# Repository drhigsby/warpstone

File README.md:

# warpstone

KLE: http://www.keyboard-layout-editor.com/#/gists/da9202c4c069f9cc00b6be29940ffcfc

 Warpstone is an 11u traditionally staggered monstrosity of a keyboard with multiple side mod and spacebar options.

* Keyboard Maintainer: [H. Bond](https://github.com/drhigsby)
* Hardware Supported: Warpstone (https://github.com/drhigsby/warpstone)
* Hardware Availability: make your own

Make example for this keyboard (after setting up your build environment):

    make warpstone:default

See the [build environment setup](https://docs.qmk.fm/#/getting_started_build_tools) and the [make instructions](https://docs.qmk.fm/#/getting_started_make_guide) for more information. Brand new to QMK? Start with our [Complete Newbs Guide](https://docs.qmk.fm/#/newbs).

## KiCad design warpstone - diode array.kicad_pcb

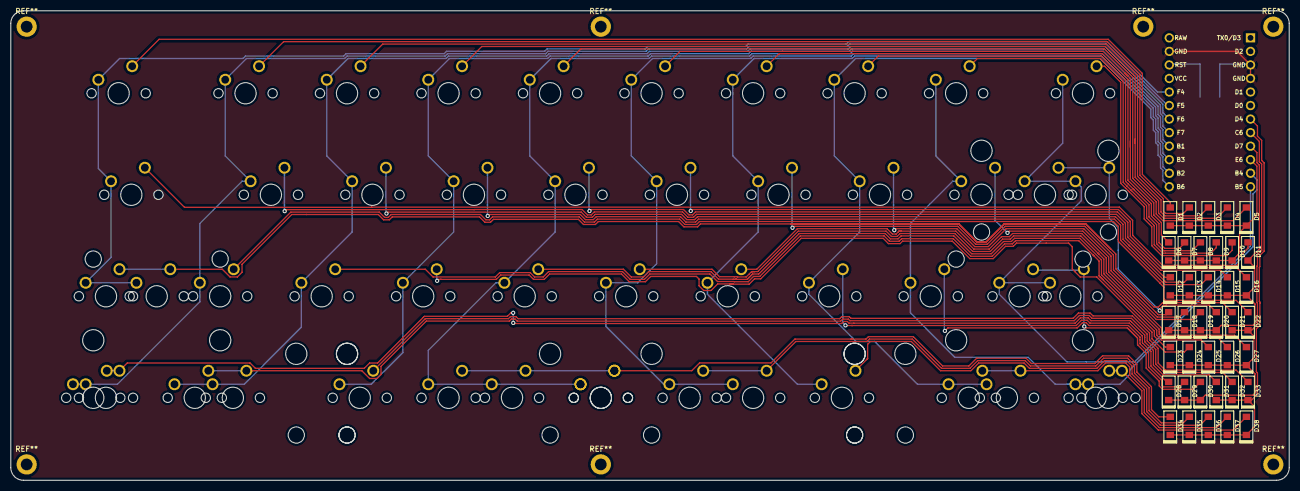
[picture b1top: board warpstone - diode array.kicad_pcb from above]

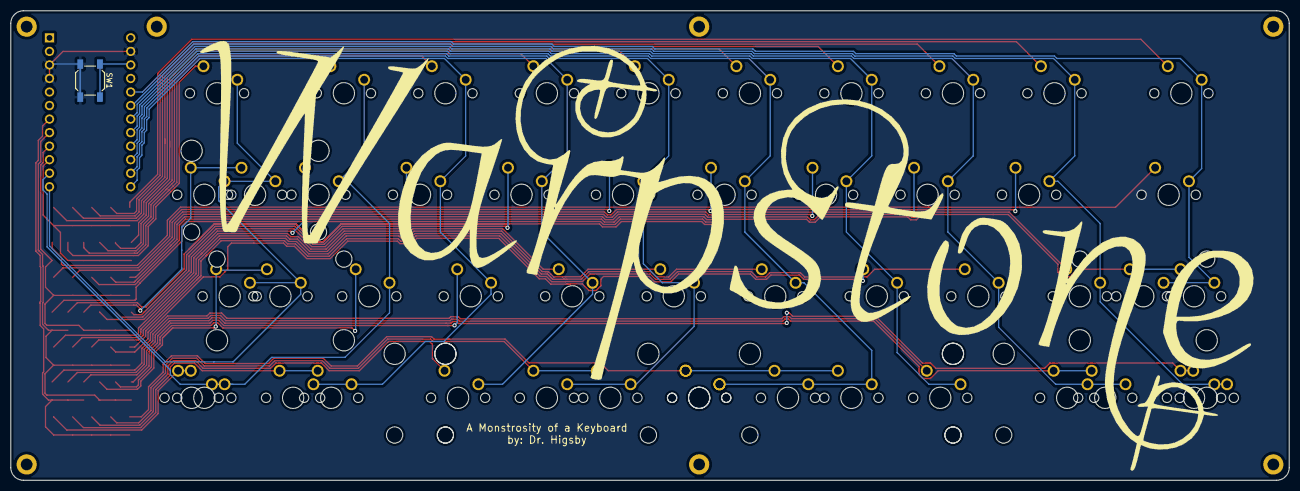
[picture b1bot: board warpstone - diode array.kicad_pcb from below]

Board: 2 copper layers, 239.9 x 88.1 mm, 89 parts (2 on the bottom side), 54 nets.

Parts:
D1, D2, D3, D4, D5, D6, D7, D8, D9, D10, D11, D12, D13, D14, D15, D16, D17, D18, D19, D20, D21, D22, D23, D24, D25, D26, D27, D28, D29, D30, D31, D32, D33, D34, D35, D36, D37, D38: D_Small; D_SOD123
MX1, MX10: MX-NoLED; MXOnly-1.5U-NoLED
MX2, MX3, MX4, MX5, MX6, MX7, MX8, MX9, MX12, MX13, MX14, MX15, MX16, MX17, MX18, MX19, MX22, MX23, MX24, MX25, MX26, MX27, MX28, MX29, MX31-1u1, MX32-1u1, MX37-1u1, MX38-1u1: MX-NoLED; MXOnly-1U-NoLED
MX11, MX30, MX34, MX35: MX-NoLED; MXOnly-1.75U-NoLED
MX20, MX21, MX31, MX32, MX33, MX36, MX37, MX38: MX-NoLED; MXOnly-1.25U-NoLED
MX20-2.25u1: MX-NoLED; MXOnly-2.25U-ReversedStabilizers-NoLED
MX21-2.25u1: MX-NoLED; MXOnly-2.25U-NoLED
MX30-2.75u1: MX-NoLED; MXOnly-2.75U-NoLED
MX34-3u1, MX35-3u1: MX-NoLED; MXOnly-3U-ReversedStabilizers-NoLED
MX34-6u1: MX-NoLED; MXOnly-6U-Centered-ReversedStabilizers-NoLED
MX34-7u1: MX-NoLED; MXOnly-7U-ReversedStabilizers-NoLED
SW1: SW_Push; SW_SPST_SKQG_WithStem
U1: ProMicro; ArduinoProMicro

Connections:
GND: SW1.2, U1.3, U1.4, U1.23
unnamed: D1.2, MX1.2
unnamed: D2.2, MX2.2
unnamed: D3.2, MX3.2
unnamed: D4.2, MX4.2
unnamed: D5.2, MX5.2
unnamed: D6.2, MX6.2
unnamed: D7.2, MX7.2
unnamed: D8.2, MX8.2
unnamed: D9.2, MX9.2
unnamed: D10.2, MX10.2
unnamed: D11.2, MX11.2
unnamed: D12.2, MX12.2
unnamed: D13.2, MX13.2
unnamed: D14.2, MX14.2
unnamed: D15.2, MX15.2
unnamed: D16.2, MX16.2
unnamed: D17.2, MX17.2
unnamed: D18.2, MX18.2
unnamed: D19.2, MX19.2
unnamed: D20.2, MX20.2, MX20-2.25u1.2
unnamed: D21.2, MX21.2, MX21-2.25u1.2
unnamed: D22.2, MX22.2
unnamed: D23.2, MX23.2
unnamed: D24.2, MX24.2
unnamed: D25.2, MX25.2
unnamed: D26.2, MX26.2
unnamed: D27.2, MX27.2
unnamed: D28.2, MX28.2
unnamed: D29.2, MX29.2
unnamed: D30.2, MX30.2, MX30-2.75u1.2
unnamed: D31.2, MX31.2, MX31-1u1.2
unnamed: D32.2, MX32.2, MX32-1u1.2
unnamed: D33.2, MX33.2
unnamed: D34.2, MX34.2, MX34-3u1.2, MX34-6u1.2, MX34-7u1.2
unnamed: D35.2, MX35.2, MX35-3u1.2
unnamed: D36.2, MX36.2
unnamed: D37.2, MX37.2, MX37-1u1.2
unnamed: D38.2, MX38.2, MX38-1u1.2
RST: SW1.1, U1.22
c1: MX1.1, MX11.1, MX21.1, MX21-2.25u1.1, U1.20
c2: MX2.1, MX12.1, MX22.1, MX31.1, MX31-1u1.1, U1.19
c3: MX3.1, MX13.1, MX23.1, MX32.1, MX32-1u1.1, U1.18
c4: MX4.1, MX14.1, MX24.1, MX33.1, U1.17
c5: MX5.1, MX15.1, MX25.1, MX34.1, MX34-3u1.1, MX34-6u1.1, MX34-7u1.1, U1.16
c6: MX6.1, MX16.1, MX26.1, MX35.1, MX35-3u1.1, U1.15
c7: MX7.1, MX17.1, MX27.1, MX36.1, U1.14
c8: MX8.1, MX18.1, MX28.1, MX37.1, MX37-1u1.1, U1.13
c9: MX9.1, MX19.1, MX29.1, MX38.1, MX38-1u1.1, U1.11
c10: MX10.1, MX20.1, MX20-2.25u1.1, MX30.1, MX30-2.75u1.1, U1.12
r1: D1.1, D2.1, D3.1, D4.1, D5.1, D6.1, D7.1, D8.1, D9.1, D10.1, U1.10
r2: D11.1, D12.1, D13.1, D14.1, D15.1, D16.1, D17.1, D18.1, D19.1, D20.1, U1.9
r3: D21.1, D22.1, D23.1, D24.1, D25.1, D26.1, D27.1, D28.1, D29.1, D30.1, U1.8
r4: D31.1, D32.1, D33.1, D34.1, D35.1, D36.1, D37.1, D38.1, U1.7

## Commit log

2021-08-31 added imgur link
2021-09-01 autosave file update
2021-09-13 updating readme
2022-03-10 overhaul
    total overhaul to the design of the board
    case design now available
    protos en route
2022-03-10 readme update
2022-03-21 few slight adjustments
    adjusted position of text in eeschema and generated new svgs for the case
2022-04-28 updates
    some more updates n stuff
2022-09-29 revert commit
2022-09-29 Revert "initial commit"
    This reverts commit 248fd84fb207d587a9f98a12e79b91eff061e50d.
